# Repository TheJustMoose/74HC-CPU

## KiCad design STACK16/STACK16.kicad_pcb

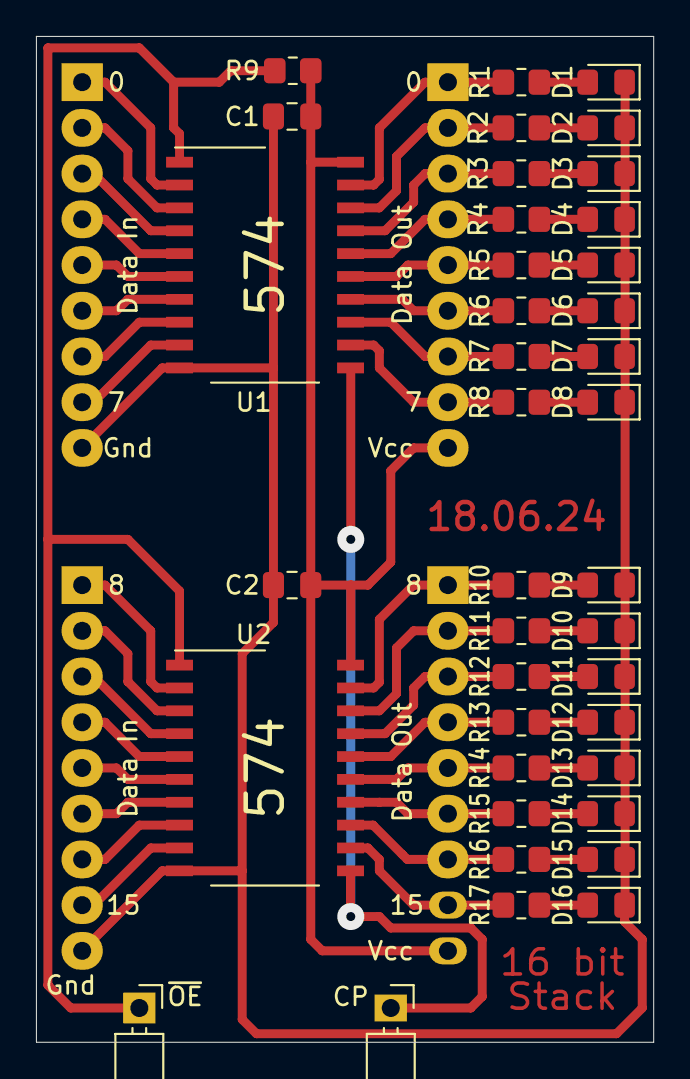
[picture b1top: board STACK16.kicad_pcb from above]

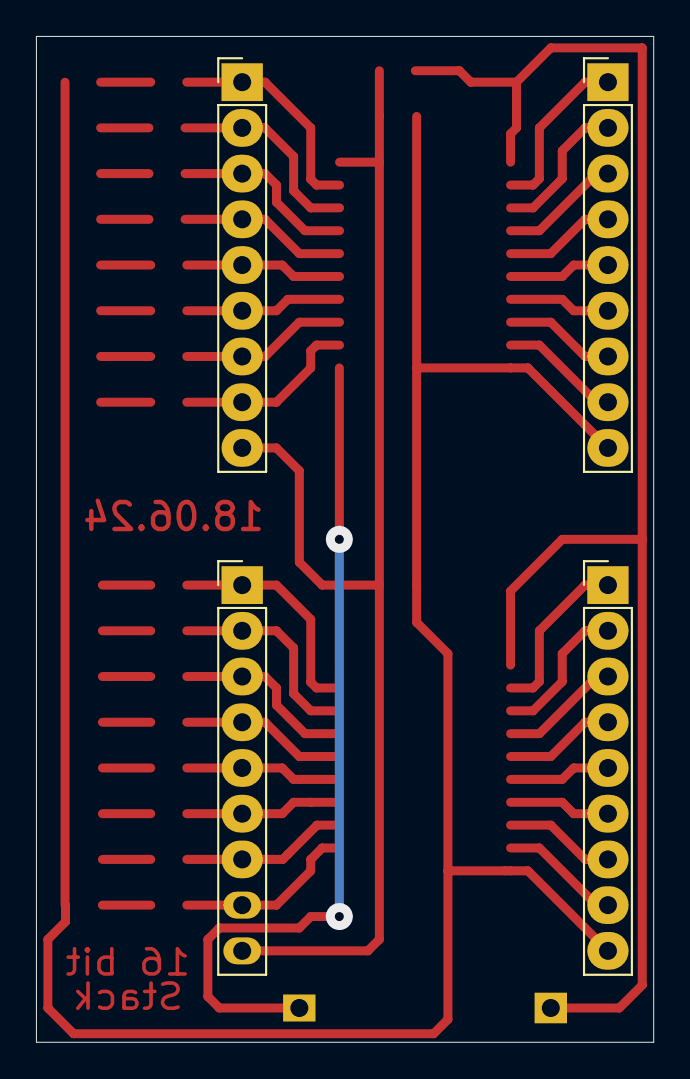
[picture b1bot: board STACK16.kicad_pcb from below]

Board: 2 copper layers, 34.3 x 55.9 mm, 43 parts (4 on the bottom side), 52 nets.

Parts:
C1, C2: 0.1uF; C_0805_2012Metric_Pad1.18x1.45mm_HandSolder
D1, D2, D3, D4, D5, D6, D7, D8, D9, D10, D11, D12, D13, D14, D15, D16: LED; LED_0805_2012Metric_Pad1.15x1.40mm_HandSolder
J1, J2, J5, J6: Conn_01x09_Male; PinHeader_1x09_P2.54mm_Vertical
J3, J4: Conn_01x01_Male; PinHeader_1x01_P2.54mm_Horizontal
R1, R2, R3, R4, R5, R6, R7, R8, R10, R11, R12, R13, R14, R15, R16, R17: 1k; R_0805_2012Metric_Pad1.20x1.40mm_HandSolder
R9: 10k; R_0805_2012Metric_Pad1.20x1.40mm_HandSolder
U1, U2: 74LS574; SO-20_12.8x7.5mm_P1.27mm

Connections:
/CP: J3.1, U1.11, U2.11
/D0: J2.1, U1.2
/D7: J2.8, U1.9
/D8: J5.1, U2.2
/D15: J5.8, U2.9
/Q0: J1.1, R1.2, U1.19
/Q1: J1.2, R2.2, U1.18
/Q2: J1.3, R3.2, U1.17
/Q3: J1.4, R4.2, U1.16
/Q4: J1.5, R5.2, U1.15
/Q5: J1.6, R6.2, U1.14
/Q6: J1.7, R7.2, U1.13
/Q7: J1.8, R8.2, U1.12
/Q8: J6.1, R10.2, U2.19
/Q9: J6.2, R11.2, U2.18
/Q10: J6.3, R12.2, U2.17
/Q11: J6.4, R13.2, U2.16
/Q12: J6.5, R14.2, U2.15
/Q13: J6.6, R15.2, U2.14
/Q14: J6.7, R16.2, U2.13
/Q15: J6.8, R17.2, U2.12
/~OE: J4.1, R9.1, U1.1, U2.1
GND: C1.2, C2.2, D1.1, D2.1, D3.1, D4.1, D5.1, D6.1, D7.1, D8.1, D9.1, D10.1, D11.1, D12.1, D13.1, D14.1, D15.1, D16.1, J2.9, J5.9, U1.10, U2.10
unnamed: D1.2, R1.1
unnamed: D2.2, R2.1
unnamed: D3.2, R3.1
unnamed: D4.2, R4.1
unnamed: D5.2, R5.1
unnamed: D6.2, R6.1
unnamed: D7.2, R7.1
unnamed: D8.2, R8.1
unnamed: D9.2, R10.1
unnamed: D10.2, R11.1
unnamed: D11.2, R12.1
unnamed: D12.2, R13.1
unnamed: D13.2, R14.1
unnamed: D14.2, R15.1
unnamed: D15.2, R16.1
unnamed: D16.2, R17.1
unnamed: J2.2, U1.3
unnamed: J2.3, U1.4
unnamed: J2.4, U1.5
unnamed: J2.5, U1.6
unnamed: J2.6, U1.7
unnamed: J2.7, U1.8
unnamed: J5.2, U2.3
unnamed: J5.3, U2.4
unnamed: J5.4, U2.5
unnamed: J5.5, U2.6
unnamed: J5.6, U2.7
unnamed: J5.7, U2.8
VCC: C1.1, C2.1, J1.9, J6.9, R9.2, U1.20, U2.20

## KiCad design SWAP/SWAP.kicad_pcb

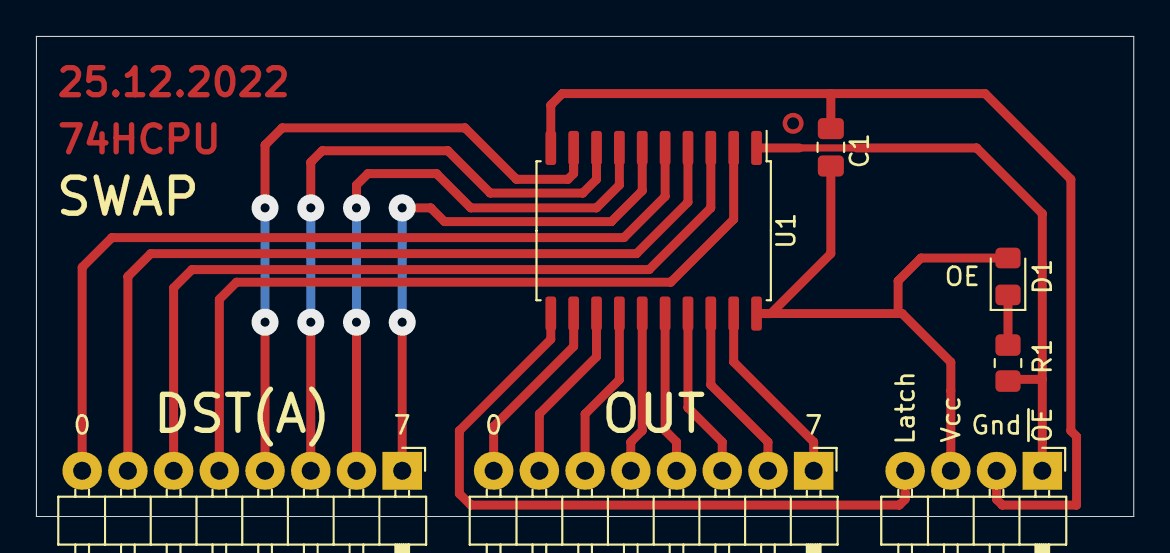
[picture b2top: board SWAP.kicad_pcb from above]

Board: 2 copper layers, 61.0 x 26.7 mm, 7 parts (0 on the bottom side), 21 nets.

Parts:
C1: 0.1uF; C_0805_2012Metric_Pad1.18x1.45mm_HandSolder
D1: LED; LED_0805_2012Metric_Pad1.15x1.40mm_HandSolder
J2, J3: Conn_01x08_Male; PinHeader_1x08_P2.54mm_Horizontal
J4: Conn_01x04_Male; PinHeader_1x04_P2.54mm_Horizontal
R1: 1k; R_0805_2012Metric_Pad1.20x1.40mm_HandSolder
U1: 74LS573; SOP-20_7.5x12.8mm_P1.27mm

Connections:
/A0: J2.8, U1.5
/A1: J2.7, U1.4
/A2: J2.6, U1.3
/A3: J2.5, U1.2
/A4: J2.4, U1.9
/A5: J2.3, U1.8
/A6: J2.2, U1.7
/A7: J2.1, U1.6
/Latch: J4.4, U1.11
/OUT0: J3.8, U1.12
/OUT7: J3.1, U1.19
/~OE: J4.1, R1.2, U1.1
GND: C1.2, J4.2, U1.10
unnamed: D1.1, R1.1
unnamed: J3.2, U1.18
unnamed: J3.3, U1.17
unnamed: J3.4, U1.16
unnamed: J3.5, U1.15
unnamed: J3.6, U1.14
unnamed: J3.7, U1.13
VCC: C1.1, D1.2, J4.3, U1.20

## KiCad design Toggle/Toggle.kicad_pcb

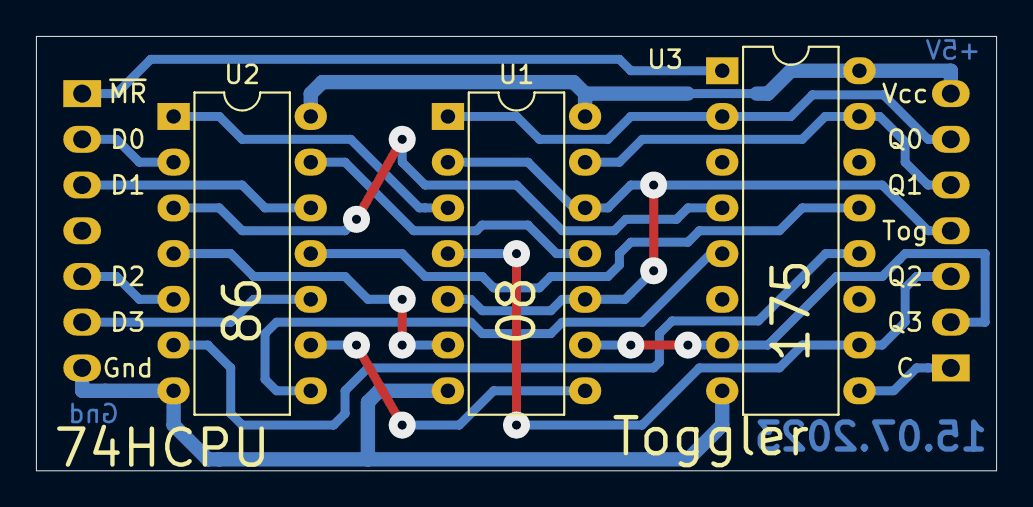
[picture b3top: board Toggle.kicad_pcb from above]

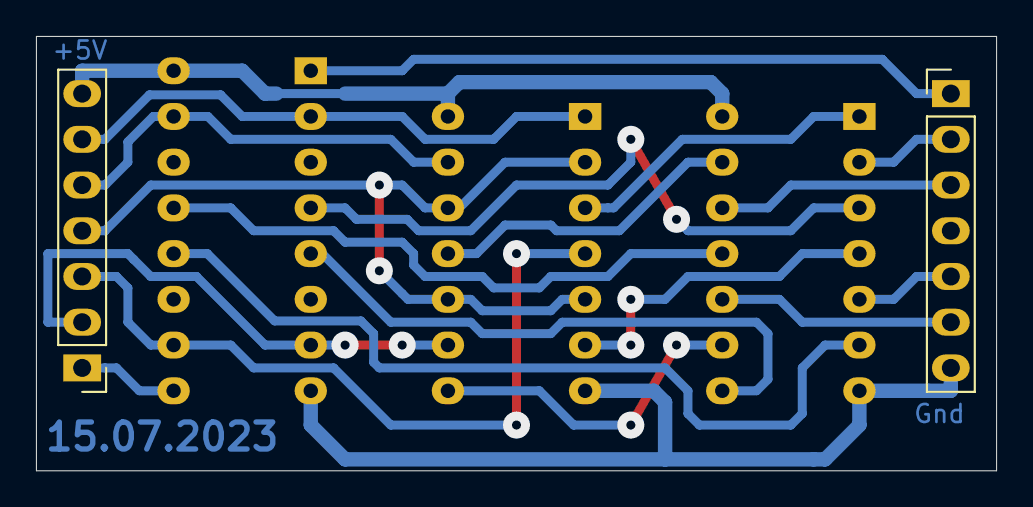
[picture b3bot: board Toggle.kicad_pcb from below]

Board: 2 copper layers, 53.3 x 24.1 mm, 5 parts (2 on the bottom side), 21 nets.

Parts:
J1, J2: Conn_01x07_Male; PinHeader_1x07_P2.54mm_Vertical
U1: 74LS08; DIP-14_W7.62mm
U2: 74LS86; DIP-14_W7.62mm
U3: 74LS175; DIP-16_W7.62mm

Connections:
/C: J2.1, U3.9
/D0: J1.2, U2.2
/D1: J1.3, U2.12
/D2: J1.5, U2.5
/D3: J1.6, U2.10
/M0: U2.3, U3.4
/M1: U2.11, U3.13
/M2: U2.6, U3.12
/M3: U2.8, U3.5
/Q0: J2.6, U1.1, U3.2
/Q1: J2.5, U1.13, U3.15
/Q2: J2.3, U1.4, U3.10
/Q3: J2.2, U1.9, U3.7
/Toggle: J2.4, U1.2, U1.5, U1.10, U1.12
/~MR: J1.1, U3.1
GND: J1.7, U1.7, U2.7, U3.8
unnamed: U1.3, U2.1
unnamed: U1.6, U2.4
unnamed: U1.8, U2.9
unnamed: U1.11, U2.13
VCC: J2.7, U1.14, U2.14, U3.16

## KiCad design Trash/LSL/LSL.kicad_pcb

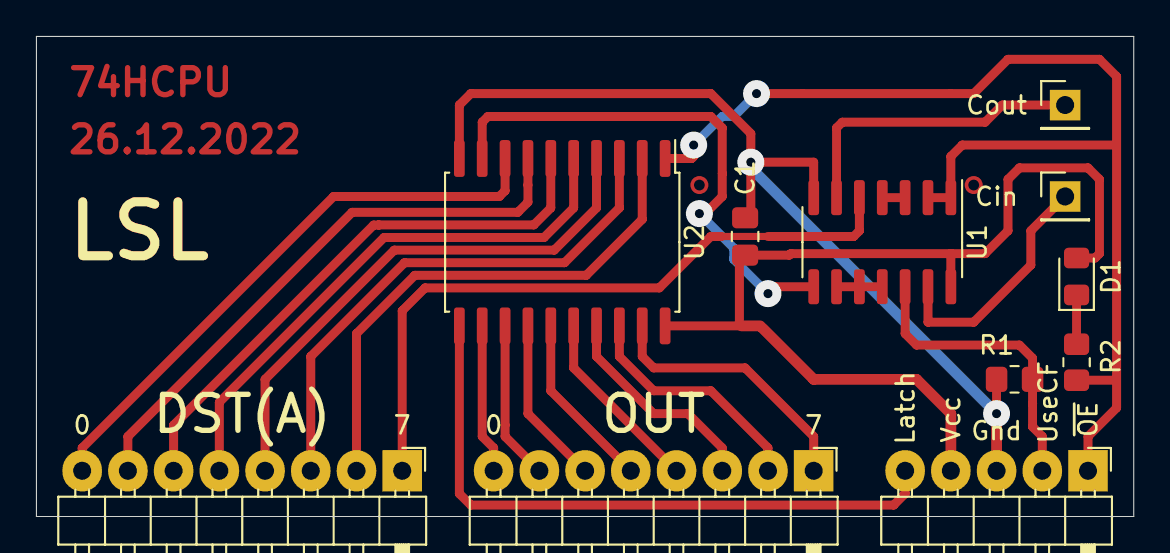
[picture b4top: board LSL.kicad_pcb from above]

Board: 2 copper layers, 61.0 x 26.7 mm, 11 parts (0 on the bottom side), 27 nets.

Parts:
C1: 0.1uF; C_0805_2012Metric_Pad1.18x1.45mm_HandSolder
D1: LED; LED_0805_2012Metric_Pad1.15x1.40mm_HandSolder
J1, J4: Conn_01x01_Male; PinHeader_1x01_P2.54mm_Vertical
J2, J3: Conn_01x08_Male; PinHeader_1x08_P2.54mm_Horizontal
J5: Conn_01x05_Male; PinHeader_1x05_P2.54mm_Horizontal
R1, R2: R; R_0805_2012Metric_Pad1.20x1.40mm_HandSolder
U1: 74HC00; SO-14_3.9x8.65mm_P1.27mm
U2: 74LS573; SOIC-20W_7.5x12.8mm_P1.27mm

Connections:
/CF_IN: J4.1, U1.13
/D0: J2.8, U2.8
/D1: J2.7, U2.7
/D2: J2.6, U2.6
/D3: J2.5, U2.5
/D4: J2.4, U2.4
/D5: J2.3, U2.3
/D6: J2.2, U2.2
/D7: J2.1, U1.5
/Latch: J5.5, U2.11
/O0: J3.8, U2.12
/O1: J3.7, U2.13
/O2: J3.6, U2.14
/O3: J3.5, U2.15
/O4: J3.4, U2.16
/O5: J3.3, U2.17
/O6: J3.2, U2.18
/O7: J3.1, U2.19
/UseCF: J5.2, R1.1, U1.12
/~(CF&OE): J1.1, U1.6
/~OE: J5.1, R2.2, U1.1, U1.2, U2.1
GND: C1.2, J5.3, R1.2, U1.7, U2.10
unnamed: D1.1, R2.1
unnamed: U1.3, U1.4
unnamed: U1.8, U2.9
unnamed: U1.9, U1.10, U1.11
VCC: C1.1, D1.2, J5.4, U1.14, U2.20

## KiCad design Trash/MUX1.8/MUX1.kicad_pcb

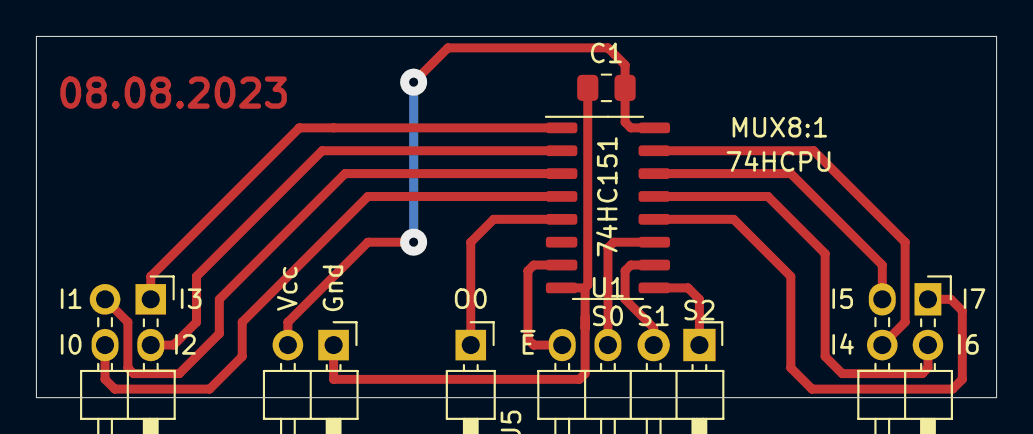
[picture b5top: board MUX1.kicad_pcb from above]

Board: 2 copper layers, 53.3 x 20.1 mm, 7 parts (0 on the bottom side), 15 nets.

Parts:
C1: C; C_0805_2012Metric_Pad1.18x1.45mm_HandSolder
J1, J2: Conn_01x04_Male; PinHeader_2x02_P2.54mm_Horizontal
J3: Conn_01x04_Male; PinHeader_1x04_P2.54mm_Horizontal
J4: Conn_01x02_Male; PinHeader_1x02_P2.54mm_Horizontal
J5: Conn_01x01_Male; PinHeader_1x01_P2.54mm_Horizontal
U1: 74LS151; SO-16_3.9x9.9mm_P1.27mm

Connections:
/I0: J1.4, U1.4
/I1: J1.3, U1.3
/I2: J1.2, U1.2
/I3: J1.1, U1.1
/I4: J2.4, U1.15
/I5: J2.3, U1.14
/I6: J2.2, U1.13
/I7: J2.1, U1.12
/O0: J5.1, U1.5
/S0: J3.3, U1.11
/S1: J3.2, U1.10
/S2: J3.1, U1.9
/~E: J3.4, U1.7
GND: C1.2, J4.1, U1.8
VCC: C1.1, J4.2, U1.16

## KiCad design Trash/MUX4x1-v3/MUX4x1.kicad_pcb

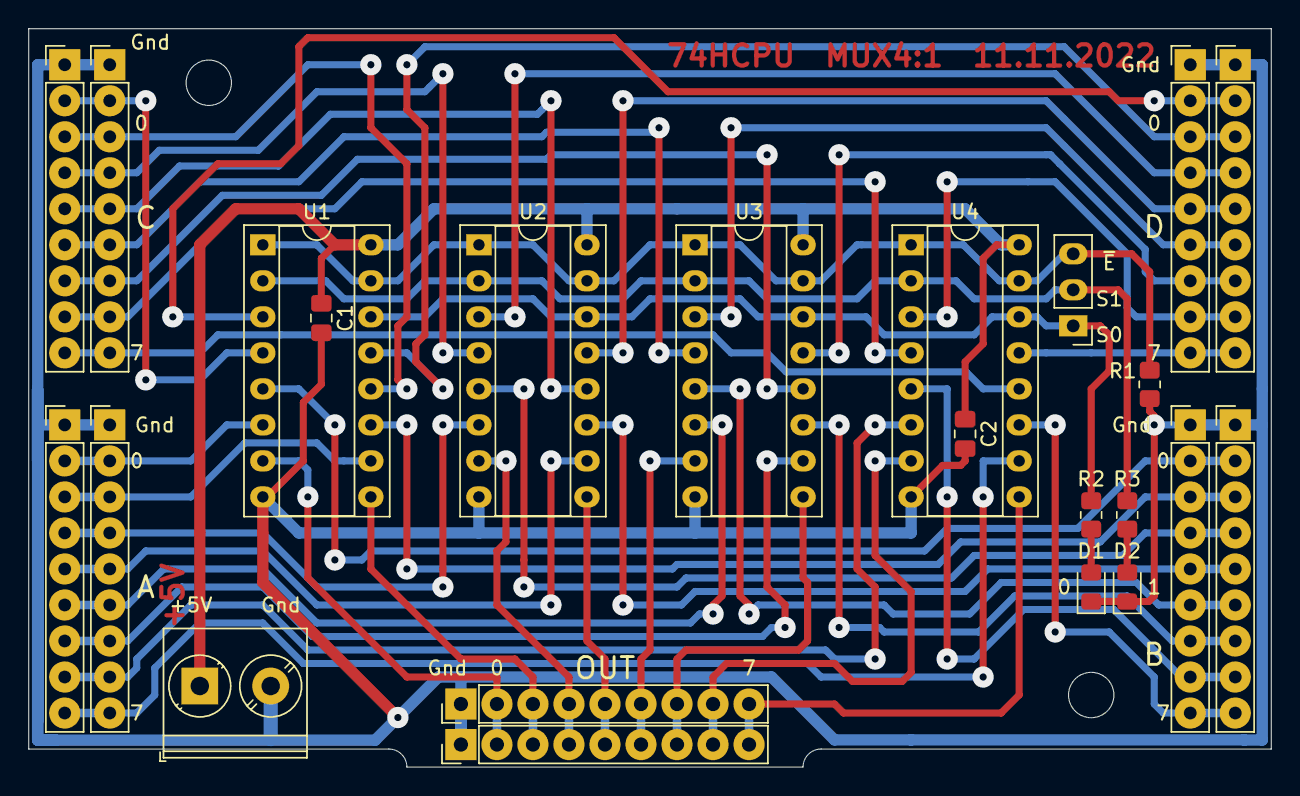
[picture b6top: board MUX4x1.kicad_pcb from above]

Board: 2 copper layers, 87.6 x 52.1 mm, 25 parts (0 on the bottom side), 47 nets.

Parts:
C1, C2: 0.1uF; C_0805_2012Metric_Pad1.18x1.45mm_HandSolder
D1, D2: LED; LED_0805_2012Metric_Pad1.15x1.40mm_HandSolder
H1, H2: MountingHole; MountingHole_3.2mm_M3
J1: Screw_Terminal_01x02; TerminalBlock_Phoenix_PT-1,5-2-5.0-H_1x02_P5.00mm_Horizontal
J2, J3, J4, J5, J6, J8, J9, J10, J11, J12: Conn_01x09_Male; PinHeader_1x09_P2.54mm_Vertical
J7: Conn_01x03_Male; PinHeader_1x03_P2.54mm_Vertical
R1: 10k; R_0805_2012Metric_Pad1.20x1.40mm_HandSolder
R2, R3: 1k; R_0805_2012Metric_Pad1.20x1.40mm_HandSolder
U1, U2, U3, U4: 74LS153; DIP-16_W7.62mm_Socket

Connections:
/A0: J2.2, J8.2, U1.6
/A1: J2.3, J8.3, U1.10
/A2: J2.4, J8.4, U2.6
/A3: J2.5, J8.5, U2.10
/A4: J2.6, J8.6, U3.6
/A5: J2.7, J8.7, U3.10
/A6: J2.8, J8.8, U4.6
/A7: J2.9, J8.9, U4.10
/B0: J3.2, J9.2, U1.5
/B1: J3.3, J9.3, U1.11
/B2: J3.4, J9.4, U2.5
/B3: J3.5, J9.5, U2.11
/B4: J3.6, J9.6, U3.5
/B5: J3.7, J9.7, U3.11
/B6: J3.8, J9.8, U4.5
/B7: J3.9, J9.9, U4.11
/C0: J4.2, J10.2, U1.4
/C1: J4.3, J10.3, U1.12
/C2: J4.4, J10.4, U2.4
/C3: J4.5, J10.5, U2.12
/C4: J4.6, J10.6, U3.4
/C5: J4.7, J10.7, U3.12
/C6: J4.8, J10.8, U4.4
/C7: J4.9, J10.9, U4.12
/D0: J5.2, J11.2, U1.3
/D1: J5.3, J11.3, U1.13
/D2: J5.4, J11.4, U2.3
/D3: J5.5, J11.5, U2.13
/D4: J5.6, J11.6, U3.3
/D5: J5.7, J11.7, U3.13
/D6: J5.8, J11.8, U4.3
/D7: J5.9, J11.9, U4.13
/O0: J6.2, J12.2, U1.7
/O1: J6.3, J12.3, U1.9
/O2: J6.4, J12.4, U2.7
/O3: J6.5, J12.5, U2.9
/O4: J6.6, J12.6, U3.7
/O5: J6.7, J12.7, U3.9
/O6: J6.8, J12.8, U4.7
/O7: J6.9, J12.9, U4.9
/S0: J7.1, R2.2, U1.14, U2.14, U3.14, U4.14
/S1: J7.2, R3.2, U1.2, U2.2, U3.2, U4.2
/~E: J7.3, R1.1, U1.1, U1.15, U2.1, U2.15, U3.1, U3.15, U4.1, U4.15
GND: C1.2, C2.2, D1.1, D2.1, J1.2, J2.1, J3.1, J4.1, J5.1, J6.1, J8.1, J9.1, J10.1, J11.1, J12.1, R1.2, U1.8, U2.8, U3.8, U4.8
unnamed: D1.2, R2.1
unnamed: D2.2, R3.1
VCC: C1.1, C2.1, J1.1, U1.16, U2.16, U3.16, U4.16
